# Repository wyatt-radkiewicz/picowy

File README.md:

# picowy Design Document
This is the design document for the picowy. This is made to be a thin, low power tomagachi like
device for my girlfriend. This design document goes over the basic system configuration and power
requirements. It enumerates every major system component. It does not go into detail about the
coding architecture, that can be found in the firmware directory.

> *eklipsed, rev. 1.0.1*

## Table of Contents
1. [Accelerometer](#accelerometer)
2. [OLED Display](#oled-display)
3. [Microcontroller](#microcontroller)
4. [Touch Panel](#touch-panel)
5. [FTDI Firmware Flasher](#ftdi-firmware-flasher)
6. [Power System](#power-system)
7. [Chassis](#chassis)

## Accelerometer
> Ultra Low-Power 3 Axis Accelerometer
- Manufacturer - *STMicroelectronics*
- Part Number - *LIS2HH12TR*
- Datasheet - [LIS2HH12](hardware/datasheets/accel/lis2hh12.pdf)
- Application Notes - [AN4662](hardware/datasheets/accel/an4662.pdf)

This accelerometer provides real world physics feedback to the simulation.
The SPI interface is used to poll acceleration data per tick of the simulation.
This uses the **Block Data Update (BDU)** feature of the LIS2HH12 to poll
data from the OUT_(X, Y, Z)_(H, L) registers while having old data be overwritten
([AN4662 Section 3.1.3](hardware/datasheets/accel/an4662.pdf#page=14)). Only the newest
data is needed, samples can be skipped since no filtering on the MCU is used.

### Parameters
- $FS=\pm4.0g$ - Measurement range in *g*
([LIS2HH12 Table 3](hardware/datasheets/accel/lis2hh12.pdf#page=10)).
- $So=0.122\frac{mg}{lsb}$ - Sensitivity in OUT registers
([LIS2HH12 Table 3](hardware/datasheets/accel/lis2hh12.pdf#page=10)).
- $ODR=50\mathrm{Hz}$ - Output data rate.
- $I_{ddA}=110\mu\mathrm{A}$ - Current consumption
([LIS2HH12 Table 4](hardware/datasheets/accel/lis2hh12.pdf#page=11)).
- $PX_G=So\times\frac{9800 mm}{s^2 \times lsb}\times\frac{128 px}{20.14 mm}
\times\frac{s}{30 ticks}=253.3\frac{px}{tick^2 \times lsb}$ -
ODR LSB to px per tick^2 conversion rate (@ 30Hz simulation rate).
  - 20.14mm - Screen size
  ([ER-OLED1.12-2 Outline Drawing](hardware/datasheets/oled/er-oled1.12-2.pdf#page=6)).

### Physics Integration
Projecting the accelerometer data onto the screen's X-Y plane is as simple as only converting
the ODR_X_HL and ODR_Y_HL registers into the screen's units and ignoring ODR_Z_HL. Multiply
ODR_X_HL and ODR_Y_HL by $PX_G$ to get the acceleration values used in the physics simulation.

Pictured below is the physical configuration of the accelerometer, where 1 is the first pin.
```
                 ^ z
                 |
               _-|-_
            _-" 1|  "-_
         _-"     |     "-_
       +-_     _-'-_     _-+
       |  "-_-"     "-_-"  |
       +-_-" "-_   _-" "-_-+
      _-" "-_   "+"   _-" "-_
  y <"       "-_ | _-"       "> x
                "+"
```
([LIS2HH12 Section 1.2](hardware/datasheets/accel/lis2hh12.pdf#page=8))

## OLED Display
> 1.12" 128x128 Monochrome White OLED Display
- Manufacturer - *EastRising*
- Part Number - *ER-OLED1.12-2W*
- Datasheet - [ER-OLED1.12-2](hardware/datasheets/oled/er-oled1.12-2.pdf)
- Reference Implementation -
[er-oled1.12-2-interfacing](hardware/datasheets/oled/er-oled1.12-2-interfacing.pdf)
- Controller - [SH1107](hardware/datasheets/oled/sh1107.pdf)
- Connector Datasheet - [ZIF20PIN](hardware/datasheets/oled/er-con20ht-1.pdf)

This OLED has a SPI interface, which can be shared with the internal measurement unit.
The 4-Wire SPI interface is selected, where A0 represents the Data/Command bit. The way that
EastRising designed the display module means that the 12V rail msut be supplied externally.

### Parameters
- $f_{SCK} = \frac{PCLK}{2} = 1.05\mathrm{MHz}$ - SPI interface speed
  - The maximum speed on the OLED's SPI interface is around 4Mhz
  ([SH1107 AC Characteristics](hardware/datasheets/oled/sh1107.pdf#page=52)).
  - The STM32 peripheral (PCLK) clock is the bottleneck. The maximum
  SPI interface speed can be set to $\frac{PCLK}{2}$
  ([RM0377 Section 26.7.1](hardware/datasheets/stm32/rm0377.pdf#page=808)).
- $IPP + IREF = 48\mu \mathrm{A}$ - Current from 12V Rail
([ER-OLED1.12-2 Section 4.3](hardware/datasheets/oled/er-oled1.12-2.pdf#page=9))
- $IDD = 100\mu \mathrm{A}$ - Current from 3.3V Rail
([ER-OLED1.12-2 Section 4.3](hardware/datasheets/oled/er-oled1.12-2.pdf#page=9))

## Microcontroller
> Arm Cortex M0+ Microcontroller 16KB Flash 2KB RAM
- Manufacturer - *STMicroelectronics*
- Part Number - *STM32L011G4U6TR*
- Datasheet - [STM32L011](hardware/datasheets/stm32/stm32l011.pdf)
- Reference Manual - [RM0377](hardware/datasheets/stm32/rm0377.pdf)
- Bootloader Manual - [AN2606](hardware/datasheets/stm32/an2606.pdf)
- USART Bootloader Protocol Manual - [AN3155](hardware/datasheets/stm32/an3155.pdf)
- Programmer's Manual - [PM0223](hardware/datasheets/stm32/pm0223.pdf)

The main program will be a state machine where it runs all functions and then sleeps. This repeats
on a main $30\mathrm{Hz}$ timer.

### Power Mode and Clock Setup
- **Power Mode (VCORE)** - To save power *VCORE Range 3 (1.2V)* will be selected
[RM0377 Section 6.1.4](hardware/datasheets/stm32/rm0377.pdf#page=138).
- **System Clock (SYSCLK)** - SYSCLK will run from the MSI (Multispeed Internal) clock at
$2.1\mathrm{MHz}$ [RM0377 Section 7.2.3](hardware/datasheets/stm32/rm0377.pdf#page=174).
- **Peripherial Clock (PCLK)** - PCLK will be run at the same frequency of $2.1\mathrm{MHz}$.
- **Run Mode** -  When running with no peripherials on except FLASH, and interpolating data from
[STM32L011 Table 22](hardware/datasheets/stm32/stm32l011.pdf#page=53), around $300\mu\mathrm{A}$ is
consumed while running.
- **Sleep Mode** - When in sleep mode running at $65\mathrm{kHz}$ and without FLASH, around
$26.5\mu\mathrm{A}$ is consumed
[STM32L011 Table 26](hardware/datasheets/stm32/stm32l011.pdf#page=56).

### States
#### 1. Wakeup
LPTIM1 is running at $30\mathrm{Hz}$, and wakes up the system.
Driven off of the stable LSI (Low Speed Internal) clock source so that MSI can be changed during
operation. System sets MSI clock back to $2.1\mathrm{MHz}$.
- **Required Peripherials:** PWR, FLASH, LPTIM1
- **Power Consumption:** $300\mu\mathrm{A} + 36.0\mu\mathrm{A} = 336.0\mu\mathrm{A}$
- **Average Runtime $\approx 0.266\mathrm{ms}$**
  - 8 cycles at 65kHz [STM32L011 Section 6.3.5](hardware/datasheets/stm32/stm32l011.pdf#page=62)
  - N cycles at 2.1Mhz (Somewhere in the 100-200 cycles range)

#### 2. Poll Touch Screen
First it runs the *Sense* operation to see if the touch screen is being touched, and only if there
is touch detected does it start up ADC1 and run the *X Pos* and *Y Pos* modes. ADC1 is configured
to run with 1.5 sample time and to run off of the PCLK with 12 bit resolution.
- **Required Peripherials:** PWR, FLASH, LPTIM1, ADC1, GPIO
- **Power Consumption:** $300\mu\mathrm{A} + 61.2\mu\mathrm{A} = 361.2\mu\mathrm{A}$
- **Average Runtime $\approx 0.122\mathrm{ms}$**
  - $1\mu\mathrm{s}$ ADC Power up Time
  [STM32L011 Table 54](hardware/datasheets/stm32/stm32l011.pdf#page=81)
  - $2\times\left(12.5 + 1.5\right)\times\frac{1}{1.05\mathrm{Mhz}}=27\mu\mathrm{s}$
  2 ADC Sample Times [STM32L011 Table 54](hardware/datasheets/stm32/stm32l011.pdf#page=81)
  - N cycles at 2.1Mhz (Somewhere in the 100-200 cycles range)

#### 3. Poll Accelerometer
SPI1 should use $CPOL=1, CPHA=1$ when communicating with the accelerometer. ODR_(X, Y, Z)_(H, L) is
read and converted into *px/tick^2* using the accelerometer's communitcation protocol
[LIS2HH12 Section 6.2](hardware/datasheets/accel/lis2hh12.pdf#page=25). With this protocol,
the ODR_X_L register can be read, and then the rest can follow with DMA1 clocking the SCK signal
for the rest.
- **Required Peripherials:** PWR, FLASH, LPTIM1, SPI1, DMA1, GPIO
- **Power Consumption:** $300\mu\mathrm{A} + 68.6\mu\mathrm{A} = 368.6\mu\mathrm{A}$
- **Average Runtime $\approx 0.291\mathrm{ms}$**
  - 56 SPI cycles
  - N cycles at 2.1Mhz (500 cycles range)

#### 4. Update Simulation
The simulation will use a state machine for the character, and the character will be affected by
the external acceleration seen by the accelerometer, and the touch sensor. It will update the
internal screen bitmap for the next step.
- **Required Peripherials:** PWR, FLASH, LPTIM1
- **Power Consumption:** $300\mu\mathrm{A} + 36.0\mu\mathrm{A} = 336.0\mu\mathrm{A}$
- **Average Runtime $\approx 4.76\mathrm{ms}$**
  - N cycles at 2.1Mhz (10,000 cycles budget)

#### 5. Update Screen
Since the 128x128 screen is too large to fit into 2KB RAM, work arounds are needed. A sprite based
approach with X, Y, W, H pairs and a reference to the bitmap in FLASH works, and with a system that
knows where sprites were previously, full screen rewrites are not needed. Even if a full screen
refresh was needed, it would only take under $18\mathrm{ms}$ when SPI1 runs at full speed
($1.05\mathrm{MHz}$).
- **Required Peripherials:** PWR, FLASH, LPTIM1, SPI1, DMA1, GPIO
- **Power Consumption:** $300\mu\mathrm{A} + 60.3\mu\mathrm{A} = 360.3\mu\mathrm{A}$
- **Average Runtime $\approx 6.19\mathrm{ms}$**
  - 4000 SPI1 cycles (Assuming 1/4 of screen is refreshed)
  - N cycles at 2.1Mhz (5,000 cycles budget)

#### 6. Sleep
This sets the MSI clock to $65\mathrm{kHz}$, disables relevant clock
blocks and peripherals, and exits the LPTIM1 interrupt to go back into sleep mode.
- **Required Peripherials:** PWR, FLASH, LPTIM1
- **Power Consumption:** $26.5\mu\mathrm{A} + 36.0\mu\mathrm{A} = 62.5\mu\mathrm{A}$

### Average Power Consumption
- Time in *Run* mode: $11.7\mathrm{ms}$
- Average current: $360\mu\mathrm{A}\times\frac{11.7}{33.33}+70\mu\mathrm{A}\times
\frac{21.63}{33.33}\approx172\mu\mathrm{A}$

### Debug Connector
> Tag Connect 2030 Solderless Connection
- Manufacturer - *Tag-Connect*
- Part Number - *TC2030*
- Datasheet - [TC2030](hardware/datasheets/conn/tc2030.pdf)

The TC2030 will be connected the STM32's SWCLK, SWDIO, 3.3V, GND, NRST. NRST will be pulled up to
$V_{DD}$. This will use the Serial Wire Debug (SWD) protocol.

## Touch Panel
> 1.44" 4 Wire Resistive Touch Screen
- Manufacturer - *EastRising*
- Part Number - *ER-TP1.44-1*
- Datasheet - [ER-TP1.44-1](hardware/datasheets/touch/er-tp1.44-1.pdf)

The datasheet doesn't contain any info on axis resistance. Design is made around that limitation,
but still the minimum and maximum allowed for the design will be selected for
$300\Omega-600\Omega$. The touch panel circuitry uses no current if the panel is not being touched.

### Diagram
- $R_{AX}$ is the axis resistance, anywhere between the minimum and maximum.
- $R_{TP}$ is current limiting resistor $R_{TP}$.
- *XL*, *YU*, *XR*, *YD* are connected to the STM32's GPIO pins.
```
   Inside TP    . To GPIO
                .
  +--------------------- XL
  |             .
  |      +-------------- YU
  |      |      .
  |     R_AX    .
  |      |      .
  +-R_AX-?-R_AX---R_TP-- XR
         |      .
        R_AX    .
         |      .
         +--------R_TP-- YD
                .
```

### Parameters
- $R_{PD} >= 25k\Omega$ - Minimum pulldown resistor value
([STM32L011 Table 50](hardware/datasheets/stm32/stm32l011.pdf#page=75)).
- $I_{MAX}=2\mathrm{mA}$

### Operation Modes
When sleeping, the touch panel GPIO is all set to Input (*no* pullup/down). This configuration
consumes no current.

#### Touch Sense
| Pin | State             |
|-----|-------------------|
| XL  | Out Push-Pull, HI |
| XR  | HZ                |
| YU  | In Pull-Down      |
| YD  | HZ                |
- $I_{TP}=\frac{V_{DD}}{R_{PD}}=0.132\mathrm{mA}$ - GPIO source/sink current (if pressed)
- $V_{TP}=V_{DD}\frac{R_{PD}}{2R_{AX}+R_{IA}+R_{PD}}=3.03\mathrm{V}$ - Touch sense level
  - $R_{IA}$ - Inter-axis touch resistance ($0-1000\Omega$)

#### X/Y Position Reading
| State | XL                | XR                | YU                | YD                |
|-------|-------------------|-------------------|-------------------|-------------------|
| X Pos | Out Push-Pull, LO | Out Push-Pull, HI | ADC In            | HZ                |
| Y Pos | ADC In            | HZ                | Out Push-Pull, LO | Out Push-Pull, HI |

$R_{TP} = 1.4\mathrm{k}\Omega$ - What to use for $R_{TP}$ since only these modes use it
- $R_{TP} > \frac{V_{DD}}{I_{MAX}}-R_{AX}$ - What to select for $R_{TP}$ to keep current low

## FTDI Firmware Flasher
> USB to UART Bridge for Firmware Flashing
- Manufacturer - *FTDI, Future Technology Devices International Ltd*
- Part Number - *FT260Q-T*
- Datasheet - [FT260](hardware/datasheets/ftdi/ft260.pdf)
- Application Notes - [AN394](hardware/datasheets/ftdi/an394.pdf)

This will be used to boot the STM32 into the USART Boot Loader
([AN3155](hardware/datasheets/stm32/an3155.pdf)). Two GPIOs will be used on the FT260, one to
assert NRST on the STM32, and the other to assert the BOOT0 pin on the STM32 to get it into
bootloader mode [AN2606 Table 2](hardware/datasheets/stm32/an2606.pdf#page=34). For this,
nBOOT_SEL must be 0 [RM0377 Section 3.7.8](hardware/datasheets/stm32/rm0377.pdf#page=110).

Support for an external EEPROM configuration chip for the FT260 will be made by making a space
for it on the PCB (need not be populated). This EEPROM chip communicates over $\mathrm{I^2C}$
[FT260 Section 9](hardware/datasheets/ftdi/ft260.pdf#page=44).

### Parameters
- $DCNF1 = 1, DCNF0 = 0$ - Only USART interface is enabled
[FT260 Section 5.1](hardware/datasheets/ftdi/ft260.pdf#page=17)
- $PARITY = EVEN$ [AN3155 Section 3](hardware/datasheets/stm32/an3155.pdf#page=9)
- $Baud\;Rate = 115200$ [AN3155 Section 2.2](hardware/datasheets/stm32/an3155.pdf#page=7)

## Power System
There are 3 distinct power rails, VBUS, 3V3, and 12V. The devices connected to each are:
| RAIL | DEVICES         | CURRENT                                                                                                       |
|------|-----------------|---------------------------------------------------------------------------------------------------------------|
| VBUS | FT260           | $9.6\mathrm{mA}$ [FT260 Table Section 6.3](hardware/datasheets/ftdi/ft260.pdf#page=29)                        |
|      | Battery Charger | $50\mathrm{mA}$ Set by $EN1=HI,EN2=LO$ [BQ24230 Section 7.5](hardware/datasheets/charger/bq24230.pdf#page=9)  |
| 3V3  | STM32           | $172\mu\mathrm{A}$ [STM32 Average Power Consumption](#microcontroller)                                        |
|      | OLED            | $100\mu\mathrm{A}$ [OLED Display 3V3 Current](#oled-display)                                                  |
|      | Accelerometer   | $110\mu\mathrm{A}$ [Accelerometer Current](#accelerometer)                                                    |
| 12V  | OLED Driver     | $32\mu\mathrm{A}$ [OLED Display Driver 12V Current](#oled-display)                                            |

The rated battery charging rate and lack of circuitry needed to negociate USB Battery Charging or
Power Delivery means that the battery charger will have an input current limit of $50\mathrm{mA}$.

With the selected parts, the 3V3 rail draws $1.4\mathrm{mW}$ because of the LDO. The 12V rail draws
$1.2\mathrm{mW}$ due to the $\approx50\%$ efficiency. This means the battery will be sourcing
around $0.7\mathrm{mA}$.

### Battery <TODO>
> 3.7V Thin Lithium Ion Battery Rechargeable
- Manufacturer - *GlobTek, Inc.*
- Part Number - *BL0105F2635161S1PCAT*
- Datasheet - [BL0105F2635161S1PCAT](hardware/datasheets/battery/battery.pdf)

Is very thin $2.8\mathrm{mm}$ thick battery, with thin connector. Stay in the $50\mathrm{mA}$ range
for charging [BL0105F2635161S1PCAT Section 3](hardware/datasheets/battery/battery.pdf#page=3).

#### Male Connector (PCB Side)
- Manufacturer - *Hirose Electric Co Ltd*
- Part Number - *DF65-3P-1.7V(21)*
- Drawing - [DF65-3P-1.7V-21](hardware/datasheets/conn/df65-3p-1.7v-21.pdf)

### Battery Charger
> Battery Charger and Power Path Managment
- Manufacturer - *Texas Instruments*
- Part Number - *BQ24230RGTR*
- Datasheet - [BQ24230](hardware/datasheets/charger/bq24230.pdf)

Using this power path battery charger, it allows instant on from a dead battery. Use custom current
limit though external resistor to give some room for the FT260 to also source current on VBUS and
to not charge the battery at its max all the time.

### Fuel Gauge
> System Side Impeadance Track Fuel Gauge
- Manufacturer - *Texas Instruments*
- Part Number - *BQ27441DRZT-G1A*
- Datasheet - [BQ27441-G1](hardware/datasheets/gauge/bq27441-g1.pdf)
- Technical Reference - [SLUUAC9A](hardware/datasheets/gauge/sluuac9a.pdf)

This is an optional component, and can be added to the $\mathrm{I^2C}$ bus on the STM32 to measure
how much battery is left and how much current the system consumes.

### 3V3 Rail
> Low Noise LDO Voltage Regulator
- Manufacturer - *Texas Instruments*
- Part Number - *TPS7A2033PDBVR*
- Datasheet - [TPS7A20](hardware/datasheets/ldo/tps7a20.pdf)

As shown the in part number, *TPS7A20***33***PDBVR* is a 3.3V low noise, low $I_Q$ LDO for
the 3.3V rail.

### 12V Rail
> Power Step-Up DC-DC Converter
- Manufacturer - *Texas Intruments*
- Part Number - *TPS61040DDCR*
- Datasheet - [TPS61040](hardware/datasheets/boost/tps61040.pdf)

The boost converter suggested by the reference implementation for the OLED. Will have around a
70% efficency a the OLED's advertised current.

## Chassis
### Front View
#### Diagram
```
          __= = = = = = = = = = = = = = =+
       _-"''"-_                          |
     ."        ".                        |
    /   +----+= =\= = = = = = = = =+     |
   /  +--------+= \ = = = = =+     |     |
  ,|  |+------+|= |.= =+     |     |     |
  /   |||    |||   \   |DISP |TPNL |BATT |A
  |   |||    |||   |   |     |     |     |
  \   |+------+|= =/= =+     |     |     |
   \  +--------+= / = = = = =+     |     |
  | "-_ +----+=_-"=|= = = = = = = =+     |
      '"-____-"'= = = = = = = = = = = = =+
  |                |
                    
  |                |
  +----------------+
          B
```
#### Dimensions
| PART                                                                                  | DIMENSION | DESCRIPTION                | SIZE (mm) |
|---------------------------------------------------------------------------------------|-----------|----------------------------|-----------|
|                                                                                       | A         | Device Height              | 70        |
|                                                                                       | B         | Device Width               | 60        |
| DISP [ER-OLED1.12-2 Section 3.1](hardware/datasheets/oled/er-oled1.12-2.pdf#page=6)   | H         | Display Height             | 30.3      |
|                                                                                       | W         | Display Width              | 27.2      |
|                                                                                       | C         | FPC Connector Length (min) | 19.15     |
| TPNL [ER-TP1.44-1](hardware/datasheets/touch/er-tp1.44-1.pdf)                         | H         | Touch Panel Height (max)   | 30.7      |
|                                                                                       | W         | Touch Panel Width (max)    | 34.9      |
|                                                                                       | C         | FPC Connector Length (min) | 9.2       |
| BATT [BL0105F2635161S1PCAT Section 8](hardware/datasheets/battery/battery.pdf#page=4) | H         | Battery Height (max)       | 37        |
|                                                                                       | W         | Battery Width (max)        | 16.5      |

### Side View
#### Diagram
```
  ________.              .________      
  __A_____|______________|________   }A
  __B___|         C         |_____ = }B= = = =]= = = = =]
        +-+---------------+-+= = = = = = = = =]C        ]H
    H     |_______D_______|          }D                 ]
  _________|      F      |________ = = = = = =]= = = = =]
  __E______|_____________|________ = }E= = = =]F
  __G_____________________________   }G
```

#### Dimensions
| DIMENSION                                                                          | DESCRIPTION                            | SIZE (mm)           |
|------------------------------------------------------------------------------------|----------------------------------------|---------------------|
| A                                                                                  | Acrylic Sheet Thickness (max)          | 1.1                 |
| B                                                                                  | Acrylic Sheet Thickness (max)          | 1.1                 |
| C [ER-TP1.44-1](hardware/datasheets/touch/er-tp1.44-1.pdf)                         | Touch Panel Thickness (max)            | 1.2 ($1.1\pm0.1$)   |
| D [ER-OLED1.12-2 Section 3.1](hardware/datasheets/oled/er-oled1.12-2.pdf#page=6)   | OLED Display Thickness (max)           | 1.35 ($1.25\pm0.1$) |
| E                                                                                  | PCB Thickness (max)                    | 1.7                 |
| F  [BL0105F2635161S1PCAT Section 8](hardware/datasheets/battery/battery.pdf#page=4)| Battery Thickness (max)                | 2.8                 |
| G                                                                                  | Acrylic Sheet Thickness (max)          | 1.1                 |

- **Full Thickness**
  - $nom = 8\mathrm{mm}$
  - $min = 7.55\mathrm{mm}$
- **PCB Acrylic Clearance** $= 2.5\pm0.35\mathrm{mm}$
- **PCB Touch Panel Clearance** $= 2.45\pm0.2\mathrm{mm}$
- **PCB OLED Clearance** $= 1.2\pm0.1\mathrm{mm}$

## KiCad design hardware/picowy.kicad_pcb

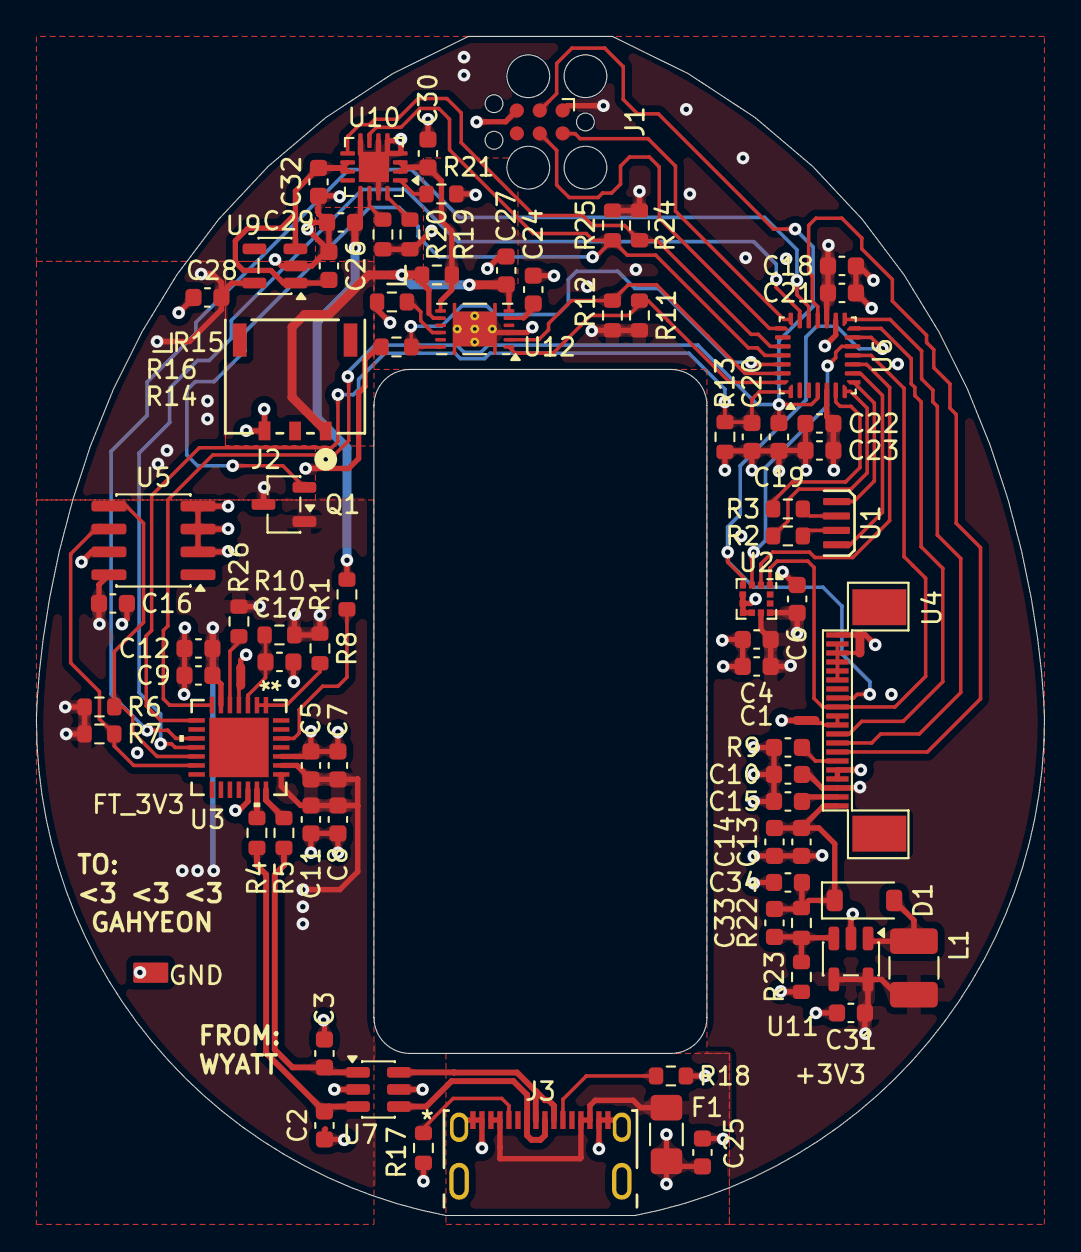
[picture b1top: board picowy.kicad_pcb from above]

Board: 4 copper layers, 56.0 x 65.5 mm, 81 parts (0 on the bottom side), 59 nets.

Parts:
C1, C5, C6, C11, C12, C13, C18, C19, C20, C23: 100n; C_0603_1608Metric
C2, C3: 47p; C_0603_1608Metric
C4, C21, C31: 10u; C_0603_1608Metric
C7, C8, C9, C14, C15, C17, C30, C32, C34: 4.7u; C_0603_1608Metric
C10, C16, C22, C25, C26, C27, C28, C29: 1u; C_0603_1608Metric
C24: 0.47u; C_0603_1608Metric
C33: 4.7p; C_0603_1608Metric
D1: STPS0530Z; D_SOD-123
F1: VBUS Polyfuse; Fuse_1206_3216Metric_Pad1.42x1.75mm_HandSolder
J1: Conn_ARM_SWD_TagConnect_TC2030; Tag-Connect_TC2030-IDC-FP_2x03_P1.27mm_Vertical
J2: Battery Connector; CONN_DF65-3P-1.7V21_HIR
J3: USB_C_Receptacle_USB2.0_14P; 2130830005_MOL
L1: 6.8u; L_1210_3225Metric_Pad1.42x2.65mm_HandSolder
NT1: OLED_GPIO_NT; NetTie-2_SMD_Pad0.5mm
NT2: FT_GPIO_GND; NetTie-2_SMD_Pad0.5mm
NT3: OLED_GPIO_NT2; NetTie-2_SMD_Pad0.5mm
Q1: PMOS; SOT-23-3
R1, R17, R18: 5.1k; R_0603_1608Metric
R2, R3: 1.4k; R_0603_1608Metric
R4, R5: 33; R_0603_1608Metric
R6, R7: 1k; R_0603_1608Metric
R8, R13, R14, R16, R21, R24, R25, R26: 10k; R_0603_1608Metric
R9: 910k; C_0603_1608Metric
R10: 4.7k; R_0603_1608Metric
R11, R12: 2.2k; R_0603_1608Metric
R15: 10m; R_0603_1608Metric
R19: 17.4k; R_0603_1608Metric
R20: 30k; R_0603_1608Metric
R22: 1.8M; R_0603_1608Metric
R23: 205k; R_0603_1608Metric
U1: ER-TP1.44-1
U2: LIS2HH12; LGA-12_2x2mm_P0.5mm
U3: FT260Q; WQFN-28_FTD
U4: ER-OLED1.12-2W; ER-CON20HT-1
U5: AT24CS04-SSHM; SOIC-8_3.9x4.9mm_P1.27mm
U6: STM32L011G4Ux; QFN-28_4x4mm_P0.5mm
U7: USBLC6-2SC6; SOT-23-6
U9: TPS7A20xxxDBV; SOT-23-5
U10: BQ24230RGT; VQFN-16-1EP_3x3mm_P0.5mm_EP1.68x1.68mm
U11: TPS61040DDC; SOT-23-5
U12: BQ27441-G1; Texas_S-PDSO-N12

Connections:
+3V3: C1.1, C4.1, C6.1, C10.1, C18.1, C21.1, C22.1, C23.1, C28.1, C31.1, J1.1 (VCC), L1.1, Q1.3 (S), R11.1, R12.2, R14.1, R24.1, R25.1, U2.9 (Vdd), U2.10 (Vdd_IO), U4.3 (VDD), U6.5 (VDDA), U6.17 (VDD), U9.5 (OUT), U11.4 (EN), U11.5 (VIN)
+12V: C13.1, C14.1, C33.1, C34.1, D1.1 (K), R22.1, U4.1 (VPP)
+BATT: C27.1, J2.1, R15.2, U12.6 (BAT), U12.8 (SRP)
/Main System/FT.SCL: R7.2, U3.13 (SDA), U5.6 (SCL)
/Main System/FT.SDA: R6.2, U3.12 (SCL), U5.5 (SDA)
/Main System/FT_D+: R5.1, U3.21 (DP)
/Main System/FT_D-: R4.2, U3.20 (DM)
/Main System/FT_VBUS_DET: R1.1, U3.26 (VBUS_DET)
/Main System/IREF: R9.1, U4.6 (IREF)
/Main System/OLED_GPIO_GND: NT1.2, U4.15 (D3), U4.16 (D4), U4.17 (D5), U4.18 (D6), U4.19 (D7)
/Main System/OLED_GPIO_GND2: NT3.2, U4.10 (~WR), U4.11 (E/~RD)
/Main System/VCOMH: C15.1, U4.2 (VCOMH)
/Main System/XR_TP: R3.1, U1.3 (XR)
/Main System/YD_TP: R2.1, U1.2 (YD)
/Power System/12V_FB: C33.2, R22.2, R23.1, U11.3 (FB)
/Power System/12V_SW: D1.2 (A), L1.2, U11.1 (SW)
/Power System/CHG_ISET: R19.2, U10.16 (ISET)
/Power System/CHG_TMR: R20.2, U10.14 (TMR)
/Power System/CHG_TS: R21.1, U10.1 (TS)
/Power System/GAUGE_BIN: R16.1, U12.10 (BIN)
/Power System/GAUGE_VDD: C24.1, U12.5 (V_{DD})
/Power System/USB_IN_D+: J3.A7 (D-), J3.B7 (D-), U7.6 (I/O1)
/Power System/USB_IN_D-: J3.A6 (D+), J3.B6 (D+), U7.4 (I/O2)
/Power System/USB_VBUS: F1.1, J3.A4 (VBUS), J3.A9 (VBUS), J3.B4 (VBUS), J3.B9 (VBUS)
BATT_IN: C30.1, R15.1, U10.2 (BAT), U10.3 (BAT), U12.7 (SRN)
BOOT0: C20.1, R13.1, U3.8 (DIO1), U6.1 (PB9)
CC1: J3.A5 (CC1), R17.2
CC2: J3.B5 (CC2), R18.2
CHG: R24.2, U6.24 (PB3), U10.9 (CHG)
DC_OLED: U4.9 (A0/DC), U6.14 (PB0)
FT_3V3: C5.1, C7.1, C8.1, C9.1, C11.1, C12.1, C16.1, Q1.1 (D), R6.1, R7.1, R8.1, R10.1, R26.1, U3.6 (VCCIO), U3.22 (VOUT3V3), U3.23 (VCCIN), U5.8 (VCC)
FT_DCNF1: R26.2, U3.5 (DCNF1)
FT_GPIO_HI: R8.2, U3.1 (DEBUGGER), U3.2 (STEST_RSTN)
FT_GPIO_LO: NT2.2, U3.4 (DCNF0)
FT_RESETN: C17.1, R10.2, U3.3 (RESETN)
GND: C1.2, C2.2, C3.2, C4.2, C5.2, C6.2, C7.2, C8.2, C9.2, C10.2, C11.2, C12.2, C13.2, C14.2, C15.2, C16.2, C17.2, C18.2, C19.2, C20.2, C21.2, C22.2, C23.2, C24.2, C25.2, C26.2, C27.2, C28.2, C29.2, C30.2, C31.2, C32.2, C34.2, J1.5 (GND), J2.3, J3.A1 (GND), J3.A12 (GND), J3.B1 (GND), J3.B12 (GND), J3.SH (SHIELD), NT1.1, NT2.1, NT3.1, R9.2, R13.2, R16.2, R17.1, R18.1, R19.1, R20.1, R21.2, R23.2, U2.5 (RES), U2.6 (GND), U2.7 (GND), U2.8 (GND), U3.19 (GND), U3.24 (AGND), U4.4 (BS1), U4.5 (BS2), U4.20 (GND), U5.2 (A1), U5.3 (A2), U5.4 (GND), U5.7 (WP), U6.16 (VSS), U7.2 (GND), U9.2 (GND), U10.4 (CE), U10.5 (EN2), U10.6 (EN1), U10.8 (VSS), U10.15 (TD), U10.17 (VSS), U11.2 (GND), U12.3 (V_{SS}), U12.13 (PAD)
GPOUT: R14.2, U6.26 (PB5), U12.12 (GPOUT)
MCU.MISO: U2.3 (SA0/SDO), U6.12 (SPI1_MISO)
MCU.MOSI: U2.4 (SDA/SDI), U4.13 (D1/MOSI), U6.13 (SPI1_MOSI)
MCU.RX: U3.11 (TXD), U6.20 (USART2_RX)
MCU.SCL: R12.1, U6.27 (I2C1_SCL), U12.2 (SCL)
MCU.SCLK: U2.1 (SCL/SPC), U4.12 (D0/SCLK), U6.11 (SPI1_SCK)
MCU.SDA: R11.2, U6.28 (I2C1_SDA), U12.1 (SDA)
MCU.SWCLK: J1.4 (SWCLK), U6.22 (SYS_SWCLK)
MCU.SWDIO: J1.2 (SWDIO), U6.21 (SYS_SWDIO)
MCU.TX: U3.10 (RXD), U6.19 (USART2_TX)
NRST: C19.1, J1.3 (~RESET), U3.7 (DIO0), U6.4 (NRST)
PGOOD: Q1.2 (G), R25.2, U6.25 (PB4), U10.7 (PGOOD)
USB_D+: C3.1, R5.2, U7.1 (I/O1)
USB_D-: C2.1, R4.1, U7.3 (I/O2)
VBUS: C25.1, C29.1, F1.2, R1.2, U7.5 (VBUS), U10.13 (IN)
VSYS: C26.1, C32.1, U9.1 (IN), U9.3 (EN), U10.10 (OUT), U10.11 (OUT)
XL: U1.1 (XL), U6.9 (PA3)
XR: R3.2, U6.6 (ADC_IN0)
YD: R2.2, U6.7 (ADC_IN1)
YU: U1.4 (YU), U6.8 (PA2)
~CS_ACCEL: U2.2 (~CS), U6.10 (PA4)
~CS_OLED: U4.7 (~CS), U6.18 (PA8)
~RES_OLED: U4.8 (~RES), U6.15 (PB1)

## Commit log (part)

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2026-05-01 Created README.md
2026-05-09 Simplified readme
2026-05-12 Main system done, debug system and power system next
2026-05-14 Only 3V3 and 12V Rail left in hardware design doc
2026-05-14 Finished version 1.0 of the design document
2026-05-15 Updated .gitignore
2026-05-15 Added accelerometer schematic
2026-05-21 finished schematic
2026-05-23 fixed power side
2026-06-06 Restarting routing
2026-06-12 Finished Board for Fabrication
2026-06-13 Got bare minimum for firmware working
2026-06-14 Trying out different things
2026-06-14 Changing to more declaritive approach
2026-06-14 Added CPU Subsystem
2026-06-15 Added RCC Subsystem
2026-06-17 Simplified NVIC interface
2026-06-17 IDEFK anymore lol
2026-06-18 Changed firmware structure
2026-06-23 Changed firmware structure again
2026-06-24 Basic firmware structure
2026-06-25 Changed structure again
